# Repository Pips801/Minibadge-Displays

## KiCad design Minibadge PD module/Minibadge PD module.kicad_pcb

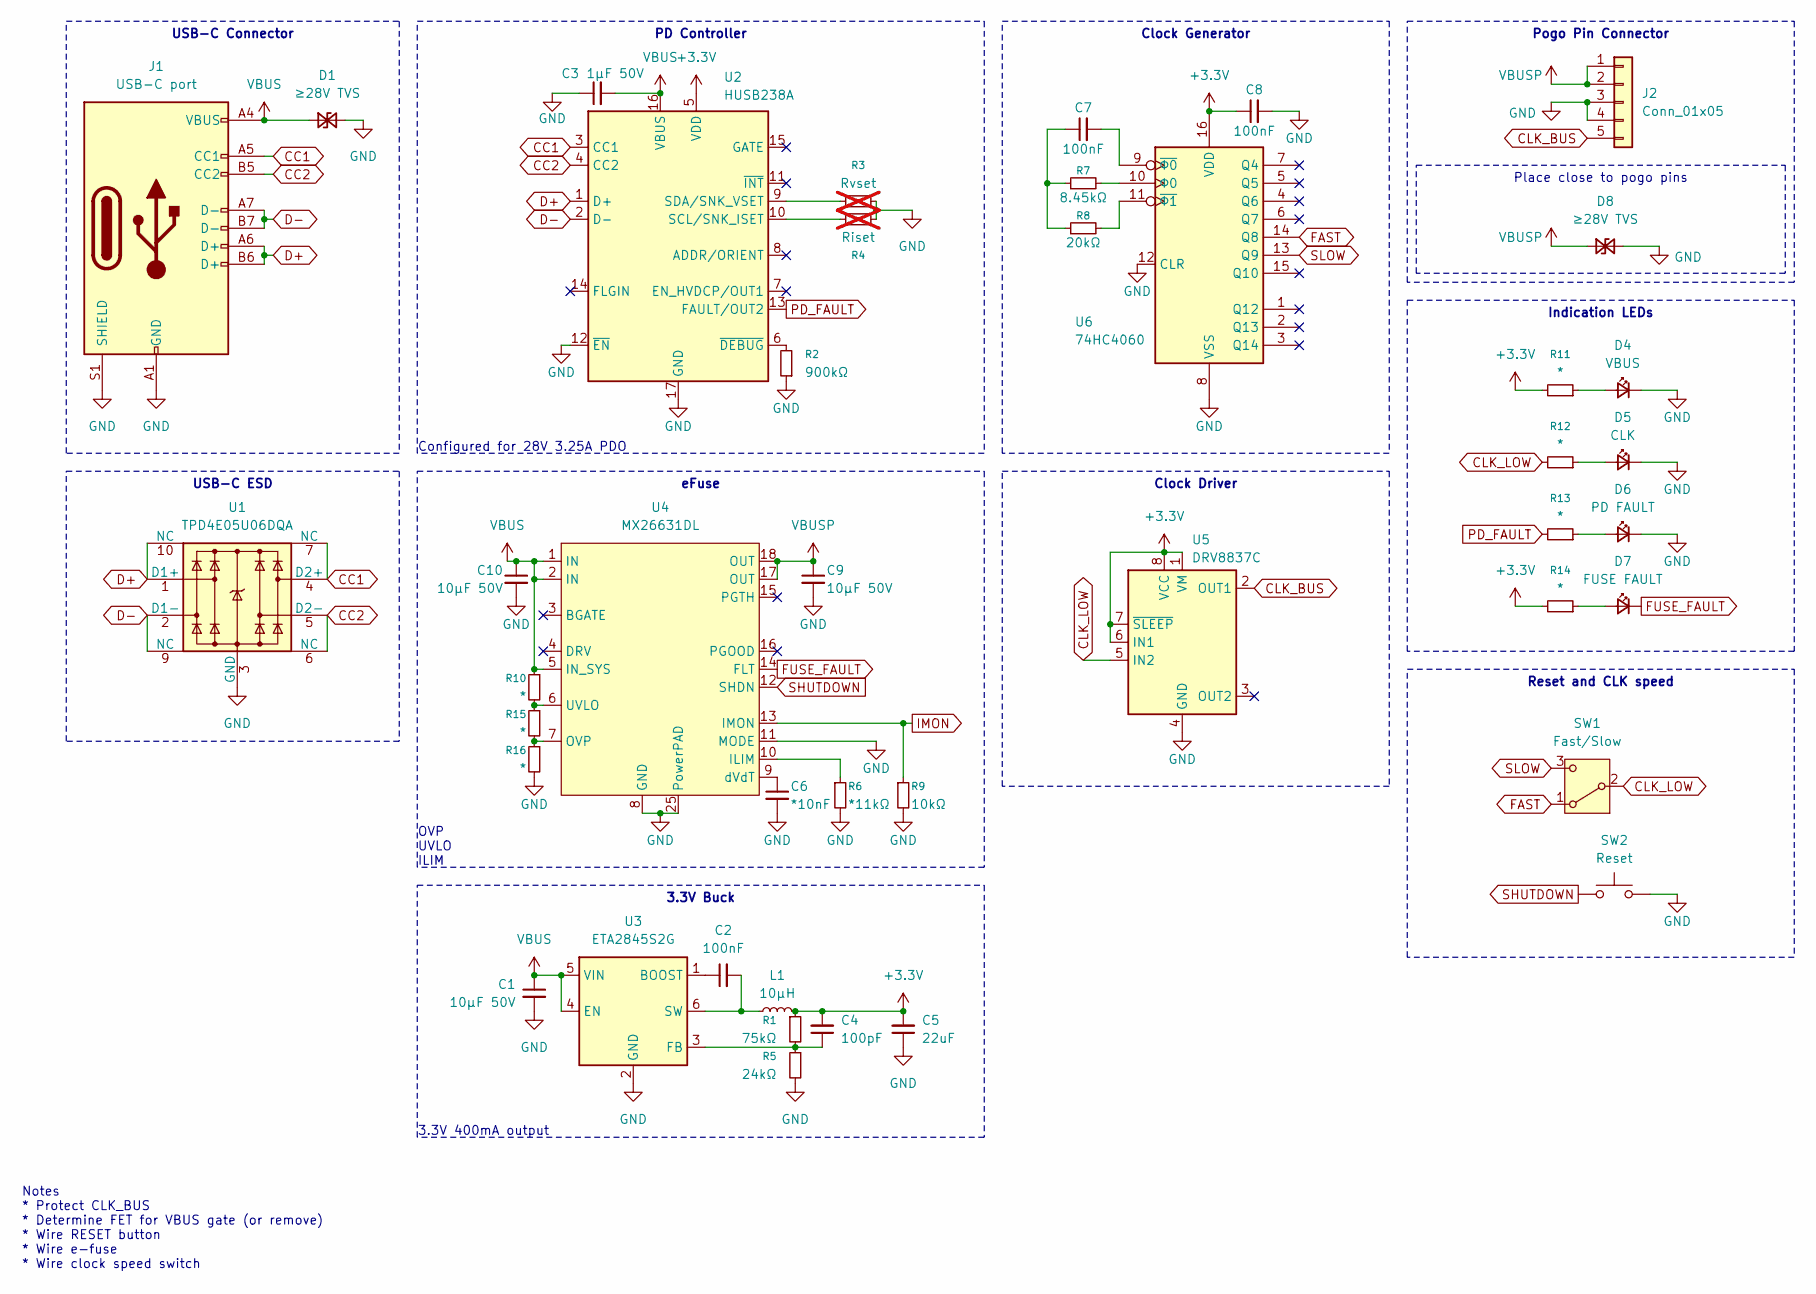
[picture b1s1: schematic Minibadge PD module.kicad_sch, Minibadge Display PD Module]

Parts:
C1, C9, C10: 10μF 50V; C_1206_3216Metric
C2, C7, C8: 100nF; C_0603_1608Metric
C3: 1μF 50V; C_0603_1608Metric
C4: 100pF; C_0603_1608Metric
C5: 22uF; C_1206_3216Metric
C6: *10nF; C_0603_1608Metric
D1, D8: ≥28V TVS; D_SMA
D4: VBUS; LED_0603_1608Metric
D5: CLK; LED_0603_1608Metric
D6: PD FAULT; LED_0603_1608Metric
D7: FUSE FAULT; LED_0603_1608Metric
J1: USB-C port; USB_C_Receptacle_HRO_TYPE-C-31-M-12
J2: Conn_01x05; PinHeader_1x05_P2.54mm_Horizontal
L1: 10μH; L_Taiyo-Yuden_MD-3030; LCSC Part # C668449
R1: 75kΩ; R_0603_1608Metric
R2: 900kΩ; R_0603_1608Metric
R3: Rvset; R_0603_1608Metric; not fitted
R4: Riset; R_0603_1608Metric; not fitted
R5: 24kΩ; R_0603_1608Metric
R6: *11kΩ; R_0603_1608Metric
R7: 8.45kΩ; R_0603_1608Metric
R8: 20kΩ; R_0603_1608Metric
R9: 10kΩ; R_0603_1608Metric
R10, R11, R12, R13, R14, R15, R16: *; R_0603_1608Metric
SW1: Fast/Slow
SW2: Reset
U1: TPD4E05U06DQA; USON-10_2.5x1.0mm_P0.5mm
U2: HUSB238A; WQFN-16-1EP_3x3mm_P0.5mm_EP1.75x1.75mm
U3: ETA2845S2G; TSOT-23-6; LCSC Part # C22362741
U4: MX26631DL; QFN-24-1EP_4x4mm_P0.5mm_EP2.6x2.6mm_ThermalVias
U5: DRV8837C; WSON-8-1EP_2x2mm_P0.5mm_EP0.9x1.6mm
U6: 74HC4060; TSSOP-16_4.4x5mm_P0.65mm

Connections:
+3.3V: C4.2, C5.2, C8.1, L1.2, R1.1, R11.2, R14.2, U2.5 (VDD), U5.1 (VM), U5.6 (IN1), U5.7 (~SLEEP), U5.8 (VCC), U6.16 (VDD)
CC1: J1.A5 (CC1), U1.4 (D2+), U1.7 (NC), U2.3 (CC1)
CC2: J1.B5 (CC2), U1.5 (D2-), U1.6 (NC), U2.4 (CC2)
CLK_BUS: J2.5, U5.2 (OUT1)
CLK_LOW: R12.2, SW1.2 (B), U5.5 (IN2)
D+: J1.A6 (D+), J1.B6 (D+), U1.1 (D1+), U1.10 (NC), U2.1 (D+)
D-: J1.A7 (D-), J1.B7 (D-), U1.2 (D1-), U1.9 (NC), U2.2 (D-)
FAST: SW1.1 (A), U6.14 (Q8)
FUSE_FAULT: D7.1 (K), U4.14 (FLT)
GND: C1.2, C3.1, C5.1, C6.2, C8.2, C9.2, C10.2, D1.2 (A2), D4.1 (K), D5.1 (K), D6.1 (K), D8.2 (A2), J1.A1 (GND), J1.A12 (GND), J1.B1 (GND), J1.B12 (GND), J1.S1 (SHIELD), J2.3, J2.4, R2.1, R3.2, R4.1, R5.2, R6.2, R9.2, R16.2, SW2.2, U1.3 (GND), U1.8 (GND), U2.12 (~EN), U2.17 (GND), U3.2 (GND), U4.8 (GND), U4.11 (MODE), U4.25 (PowerPAD), U5.4 (GND), U5.9 (GND), U6.8 (VSS), U6.12 (CLR)
IMON: R9.1, U4.13 (IMON)
unnamed: C7.1, R7.1, R8.1
unnamed: D4.2 (A), R11.1
unnamed: D5.2 (A), R12.1
unnamed: D6.2 (A), R13.1
unnamed: D7.2 (A), R14.1
unnamed: R4.2, U2.10 (SCL/SNK_ISET)
unnamed: R3.1, U2.9 (SDA/SNK_VSET)
unnamed: R2.2, U2.6 (~DEBUG)
unnamed: C2.1, U3.1 (BOOST)
unnamed: C4.1, R1.2, R5.1, U3.3 (FB)
unnamed: C2.2, L1.1, U3.6 (SW)
unnamed: R6.1, U4.10 (ILIM)
unnamed: R15.2, R16.1, U4.7 (OVP)
unnamed: R10.2, R15.1, U4.6 (UVLO)
unnamed: C6.1, U4.9 (dVdT)
unnamed: C7.2, U6.9 (~Φ0)
unnamed: R8.2, U6.11 (~Φ1)
unnamed: R7.2, U6.10 (Φ0)
PD_FAULT: R13.2, U2.13 (FAULT/OUT2)
SHUTDOWN: SW2.1, U4.12 (SHDN)
SLOW: SW1.3 (C), U6.13 (Q9)
VBUS: C1.1, C3.2, C10.1, D1.1 (A1), J1.A4 (VBUS), J1.A9 (VBUS), J1.B4 (VBUS), J1.B9 (VBUS), R10.1, U2.16 (VBUS), U3.4 (EN), U3.5 (VIN), U4.1 (IN), U4.2 (IN), U4.5 (IN_SYS)
VBUSP: C9.1, D8.1 (A1), J2.1, J2.2, U4.17 (OUT), U4.18 (OUT)

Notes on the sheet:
OVP UVLO ILIM
3.3V 400mA output
Notes * Protect CLK_BUS * Determine FET for VBUS gate (or remove) * Wire RESET button * Wire e-fuse * Wire clock speed switch
Configured for 28V 3.25A PDO
Reset and CLK speed
3.3V Buck
USB-C Connector
USB-C ESD
Clock Generator
Clock Driver
eFuse
Pogo Pin Connector
Indication LEDs
PD Controller
Place close to pogo pins

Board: 2 copper layers, 41 parts (0 on the bottom side), 31 nets, no tracks yet.

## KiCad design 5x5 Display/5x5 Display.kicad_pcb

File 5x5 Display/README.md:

# 5x5 Tileable Minibadge Display

## Details

A magnetically tileable 5x5 Minibadge display designed around USB-C PD input. This board accepts 5V - 28V and carries that voltage as the backplane for connected boards. Power input is regulated to 5V and 3.3V per board. It features a wide range of protections for shorts, over/under voltage, hotplugging, and ESD. 

### Features
* Wide voltage range input for various PD VBUS voltages (5V - 28V)
* Modular tileability using magnetic pogo pins
* Backplane scaleable to many hundreds of minibadges across many pannels

### Specifications
**Parameter**|**Value**
:-----:|:-----:
Input voltage|5V – 28V (USB-C PD)
Max input current|3.2A (Fuse-limited)
Minibadge rails|3.3V, 5V, CLK
Max output current|3.3V@3A, 5V@3A
Typical load|~13 W per board (3.3V@150mA per badge) 
Sockets|25 minibadges (5×5)
Indication|5V, 3V, CLK
Protection methods|TVS on connectors, ESD for CLK, Reverse polarity, Short protection

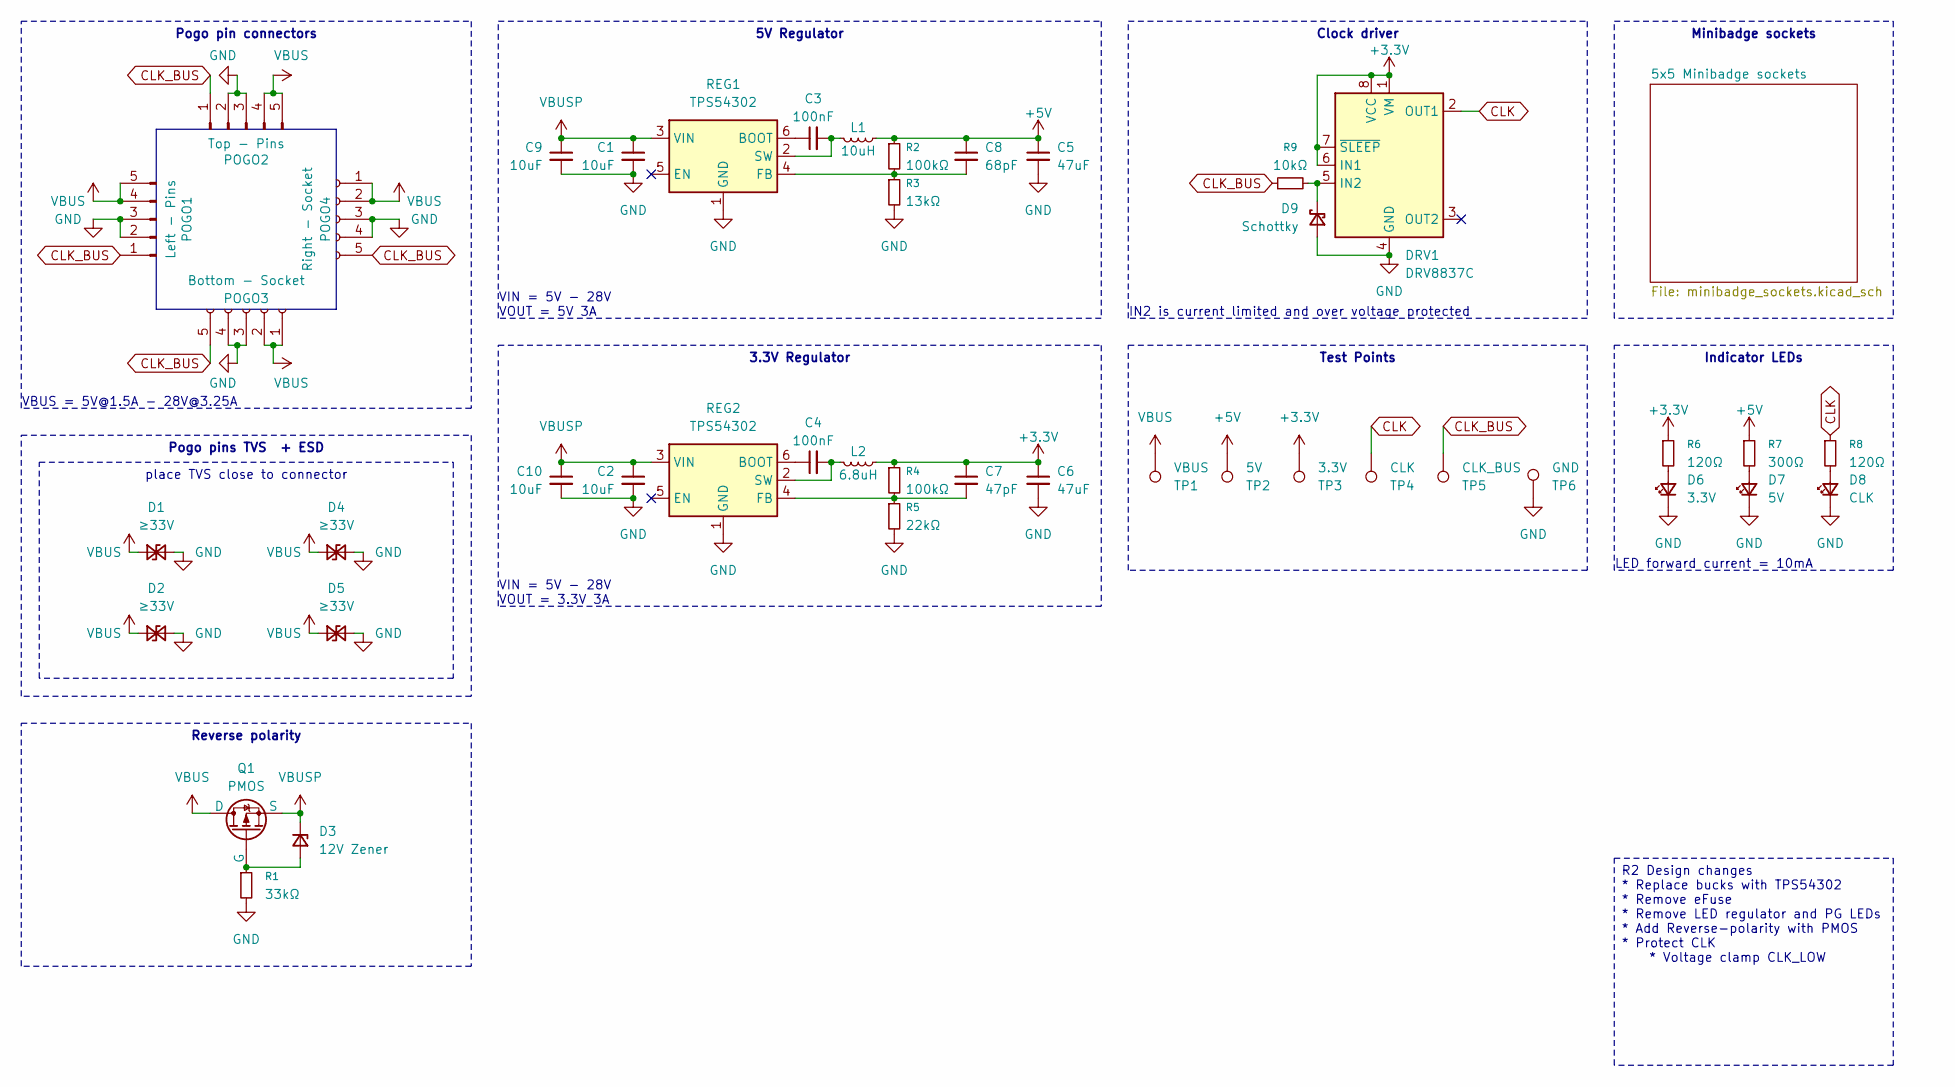
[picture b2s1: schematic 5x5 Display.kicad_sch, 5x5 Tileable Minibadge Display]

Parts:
C1, C2, C9, C10: 10uF; C_1206_3216Metric; LCSC Part # C13585
C3, C4: 100nF; C_0805_2012Metric; LCSC Part # C28233
C5, C6: 47uF; C_1206_3216Metric; LCSC Part # C96123
C7: 47pF; C_0603_1608Metric; LCSC Part # C1671
C8: 68pF; C_0603_1608Metric; LCSC Part # C28262
D1, D2, D4, D5: ≥33V; D_SMA; LCSC Part # C134981
D3: 12V Zener; D_SOD-123; LCSC Part # C22435092
D6: 3.3V; LED_0805_2012Metric; LCSC Part # C84256
D7: 5V; LED_0805_2012Metric; LCSC Part # C84256
D8: CLK; LED_0805_2012Metric; LCSC Part # C84256
D9: Schottky; D_SOD-123; LCSC Part # C7420325
DRV1: DRV8837C; WSON-8-1EP_2x2mm_P0.5mm_EP0.9x1.6mm; LCSC Part # C191000
L1: 10uH; L_TechFuse_SL0630; LCSC Part # C5189958
L2: 6.8uH; L_TechFuse_SL0630; LCSC Part # C5189749
POGO1: Left - Pins; PinSocket_1x05_P2.54mm_Horizontal
POGO2: Top - Pins; PinSocket_1x05_P2.54mm_Horizontal
POGO3: Bottom - Socket; PinSocket_1x05_P2.54mm_Horizontal
POGO4: Right - Socket; PinSocket_1x05_P2.54mm_Horizontal
Q1: PMOS; PQFN-8-EP_6x5mm_P1.27mm_Generic; LCSC Part # C51625746
R1: 33kΩ; R_0805_2012Metric
R2, R4: 100kΩ; R_0805_2012Metric; LCSC Part # C149504
R3: 13kΩ; R_0805_2012Metric; LCSC Part # C17455
R5: 22kΩ; R_0805_2012Metric; LCSC Part # C17560
R6, R8: 120Ω; R_0805_2012Metric; LCSC Part # C17437
R7: 300Ω; R_0805_2012Metric; LCSC Part # C17617
R9: 10kΩ; R_0805_2012Metric; LCSC Part # C17414
REG1, REG2: TPS54302; SOT-23-6; LCSC Part # C311983
TP1: VBUS; TestPoint_Pad_D1.5mm
TP2: 5V; TestPoint_Pad_D1.5mm
TP3: 3.3V; TestPoint_Pad_D1.5mm
TP4: CLK; TestPoint_Pad_D1.5mm
TP5: CLK_BUS; TestPoint_Pad_D1.5mm
TP6: GND; TestPoint_Pad_D1.5mm

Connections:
+3.3V: C6.1, C7.1, DRV1.1 (VM), DRV1.6 (IN1), DRV1.7 (~SLEEP), DRV1.8 (VCC), L2.2, R4.1, R6.1, TP3.1; also elsewhere on the board
+5V: C5.1, C8.1, L1.2, R2.1, R7.1, TP2.1; also elsewhere on the board
CLK: DRV1.2 (OUT1), R8.1, TP4.1; also elsewhere on the board
CLK_BUS: POGO1.1, POGO2.1, POGO3.5, POGO4.5, R9.1, TP5.1
GND: C1.2, C2.2, C5.2, C6.2, C9.2, C10.2, D1.2 (A2), D2.2 (A2), D4.2 (A2), D5.2 (A2), D6.1 (K), D7.1 (K), D8.1 (K), D9.2 (A), DRV1.4 (GND), DRV1.9 (GND), POGO1.2, POGO1.3, POGO2.2, POGO2.3, POGO3.3, POGO3.4, POGO4.3, POGO4.4, R1.2, R3.2, R5.2, REG1.1 (GND), REG2.1 (GND), TP6.1; also elsewhere on the board
unnamed: D3.2 (A), Q1.4 (G), R1.1
unnamed: D6.2 (A), R6.2
unnamed: D7.2 (A), R7.2
unnamed: D8.2 (A), R8.2
unnamed: D9.1 (K), DRV1.5 (IN2), R9.2
unnamed: C3.1, REG1.6 (BOOT)
unnamed: C8.2, R2.2, R3.1, REG1.4 (FB)
unnamed: C3.2, L1.1, REG1.2 (SW)
unnamed: C4.1, REG2.6 (BOOT)
unnamed: C7.2, R4.2, R5.1, REG2.4 (FB)
unnamed: C4.2, L2.1, REG2.2 (SW)
VBUS: D1.1 (A1), D2.1 (A1), D4.1 (A1), D5.1 (A1), POGO1.4, POGO1.5, POGO2.4, POGO2.5, POGO3.1, POGO3.2, POGO4.1, POGO4.2, Q1.5 (D), Q1.6 (D), Q1.7 (D), Q1.8 (D), Q1.9 (D), TP1.1
VBUSP: C1.1, C2.1, C9.1, C10.1, D3.1 (K), Q1.1 (S), Q1.2 (S), Q1.3 (S), REG1.3 (VIN), REG2.3 (VIN)

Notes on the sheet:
LED forward current = 10mA
VBUS = 5V@1.5A - 28V@3.25A
VIN = 5V - 28V VOUT = 5V 3A
IN2 is current limited and over voltage protected
VIN = 5V - 28V VOUT = 3.3V 3A
3.3V Regulator
Reverse polarity
Clock driver
place TVS close to connector
Test Points
Indicator LEDs
Pogo pins TVS + ESD
Pogo pin connectors
Minibadge sockets
R2 Design changes * Replace bucks with TPS54302 * Remove eFuse * Remove LED regulator and PG LEDs * Add Reverse-polarity with PMOS * Protect CLK * Voltage clamp CLK_LOW
5V Regulator

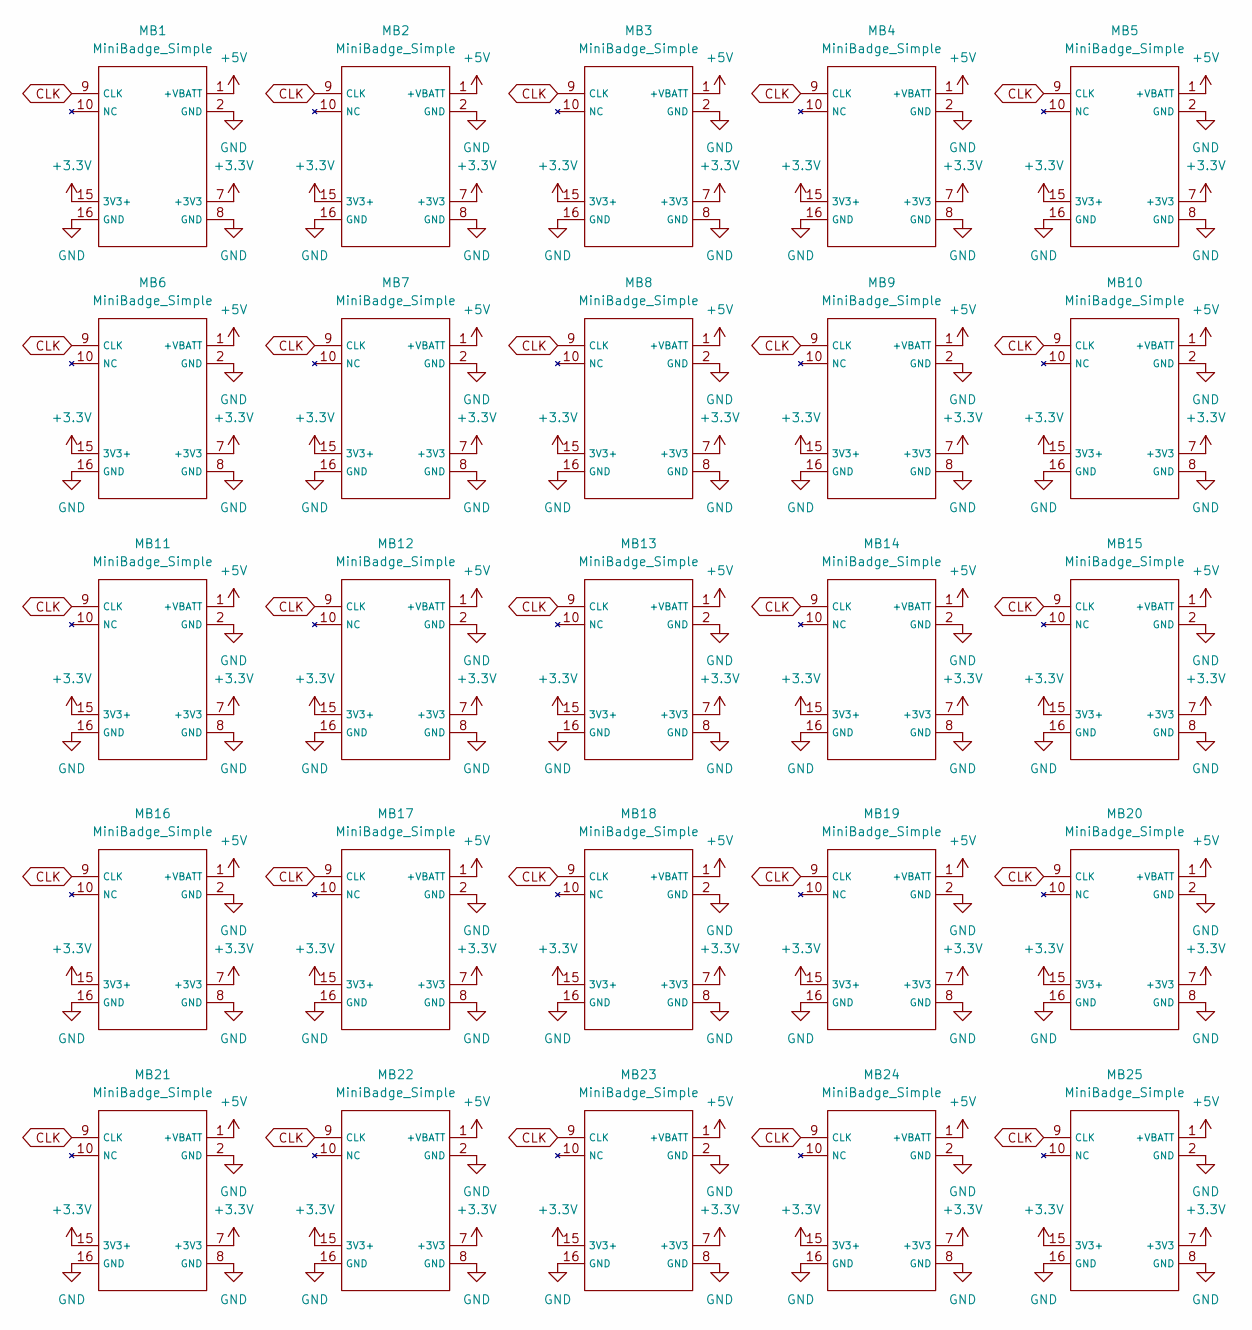
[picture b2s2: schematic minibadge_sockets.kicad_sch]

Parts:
MB1, MB2, MB3, MB4, MB5, MB6, MB7, MB8, MB9, MB10, MB11, MB12, MB13, MB14, MB15, MB16, MB17, MB18, MB19, MB20, MB21, MB22, MB23, MB24, MB25: MiniBadge_Simple; MiniBadge_Slot_Reflective

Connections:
+3.3V: MB1.7 (+3V3), MB1.15 (3V3+), MB2.7 (+3V3), MB2.15 (3V3+), MB3.7 (+3V3), MB3.15 (3V3+), MB4.7 (+3V3), MB4.15 (3V3+), MB5.7 (+3V3), MB5.15 (3V3+), MB6.7 (+3V3), MB6.15 (3V3+), MB7.7 (+3V3), MB7.15 (3V3+), MB8.7 (+3V3), MB8.15 (3V3+), MB9.7 (+3V3), MB9.15 (3V3+), MB10.7 (+3V3), MB10.15 (3V3+), MB11.7 (+3V3), MB11.15 (3V3+), MB12.7 (+3V3), MB12.15 (3V3+), MB13.7 (+3V3), MB13.15 (3V3+), MB14.7 (+3V3), MB14.15 (3V3+), MB15.7 (+3V3), MB15.15 (3V3+), MB16.7 (+3V3), MB16.15 (3V3+), MB17.7 (+3V3), MB17.15 (3V3+), MB18.7 (+3V3), MB18.15 (3V3+), MB19.7 (+3V3), MB19.15 (3V3+), MB20.7 (+3V3), MB20.15 (3V3+), MB21.7 (+3V3), MB21.15 (3V3+), MB22.7 (+3V3), MB22.15 (3V3+), MB23.7 (+3V3), MB23.15 (3V3+), MB24.7 (+3V3), MB24.15 (3V3+), MB25.7 (+3V3), MB25.15 (3V3+); also elsewhere on the board
+5V: MB1.1 (+VBATT), MB2.1 (+VBATT), MB3.1 (+VBATT), MB4.1 (+VBATT), MB5.1 (+VBATT), MB6.1 (+VBATT), MB7.1 (+VBATT), MB8.1 (+VBATT), MB9.1 (+VBATT), MB10.1 (+VBATT), MB11.1 (+VBATT), MB12.1 (+VBATT), MB13.1 (+VBATT), MB14.1 (+VBATT), MB15.1 (+VBATT), MB16.1 (+VBATT), MB17.1 (+VBATT), MB18.1 (+VBATT), MB19.1 (+VBATT), MB20.1 (+VBATT), MB21.1 (+VBATT), MB22.1 (+VBATT), MB23.1 (+VBATT), MB24.1 (+VBATT), MB25.1 (+VBATT); also elsewhere on the board
CLK: MB1.9 (CLK), MB2.9 (CLK), MB3.9 (CLK), MB4.9 (CLK), MB5.9 (CLK), MB6.9 (CLK), MB7.9 (CLK), MB8.9 (CLK), MB9.9 (CLK), MB10.9 (CLK), MB11.9 (CLK), MB12.9 (CLK), MB13.9 (CLK), MB14.9 (CLK), MB15.9 (CLK), MB16.9 (CLK), MB17.9 (CLK), MB18.9 (CLK), MB19.9 (CLK), MB20.9 (CLK), MB21.9 (CLK), MB22.9 (CLK), MB23.9 (CLK), MB24.9 (CLK), MB25.9 (CLK); also elsewhere on the board
GND: MB1.2 (GND), MB1.8 (GND), MB1.16 (GND), MB2.2 (GND), MB2.8 (GND), MB2.16 (GND), MB3.2 (GND), MB3.8 (GND), MB3.16 (GND), MB4.2 (GND), MB4.8 (GND), MB4.16 (GND), MB5.2 (GND), MB5.8 (GND), MB5.16 (GND), MB6.2 (GND), MB6.8 (GND), MB6.16 (GND), MB7.2 (GND), MB7.8 (GND), MB7.16 (GND), MB8.2 (GND), MB8.8 (GND), MB8.16 (GND), MB9.2 (GND), MB9.8 (GND), MB9.16 (GND), MB10.2 (GND), MB10.8 (GND), MB10.16 (GND), MB11.2 (GND), MB11.8 (GND), MB11.16 (GND), MB12.2 (GND), MB12.8 (GND), MB12.16 (GND), MB13.2 (GND), MB13.8 (GND), MB13.16 (GND), MB14.2 (GND), MB14.8 (GND), MB14.16 (GND), MB15.2 (GND), MB15.8 (GND), MB15.16 (GND), MB16.2 (GND), MB16.8 (GND), MB16.16 (GND), MB17.2 (GND), MB17.8 (GND), MB17.16 (GND), MB18.2 (GND), MB18.8 (GND), MB18.16 (GND), MB19.2 (GND), MB19.8 (GND), MB19.16 (GND), MB20.2 (GND), MB20.8 (GND), MB20.16 (GND), MB21.2 (GND), MB21.8 (GND), MB21.16 (GND), MB22.2 (GND), MB22.8 (GND), MB22.16 (GND), MB23.2 (GND), MB23.8 (GND), MB23.16 (GND), MB24.2 (GND), MB24.8 (GND), MB24.16 (GND), MB25.2 (GND), MB25.8 (GND), MB25.16 (GND); also elsewhere on the board

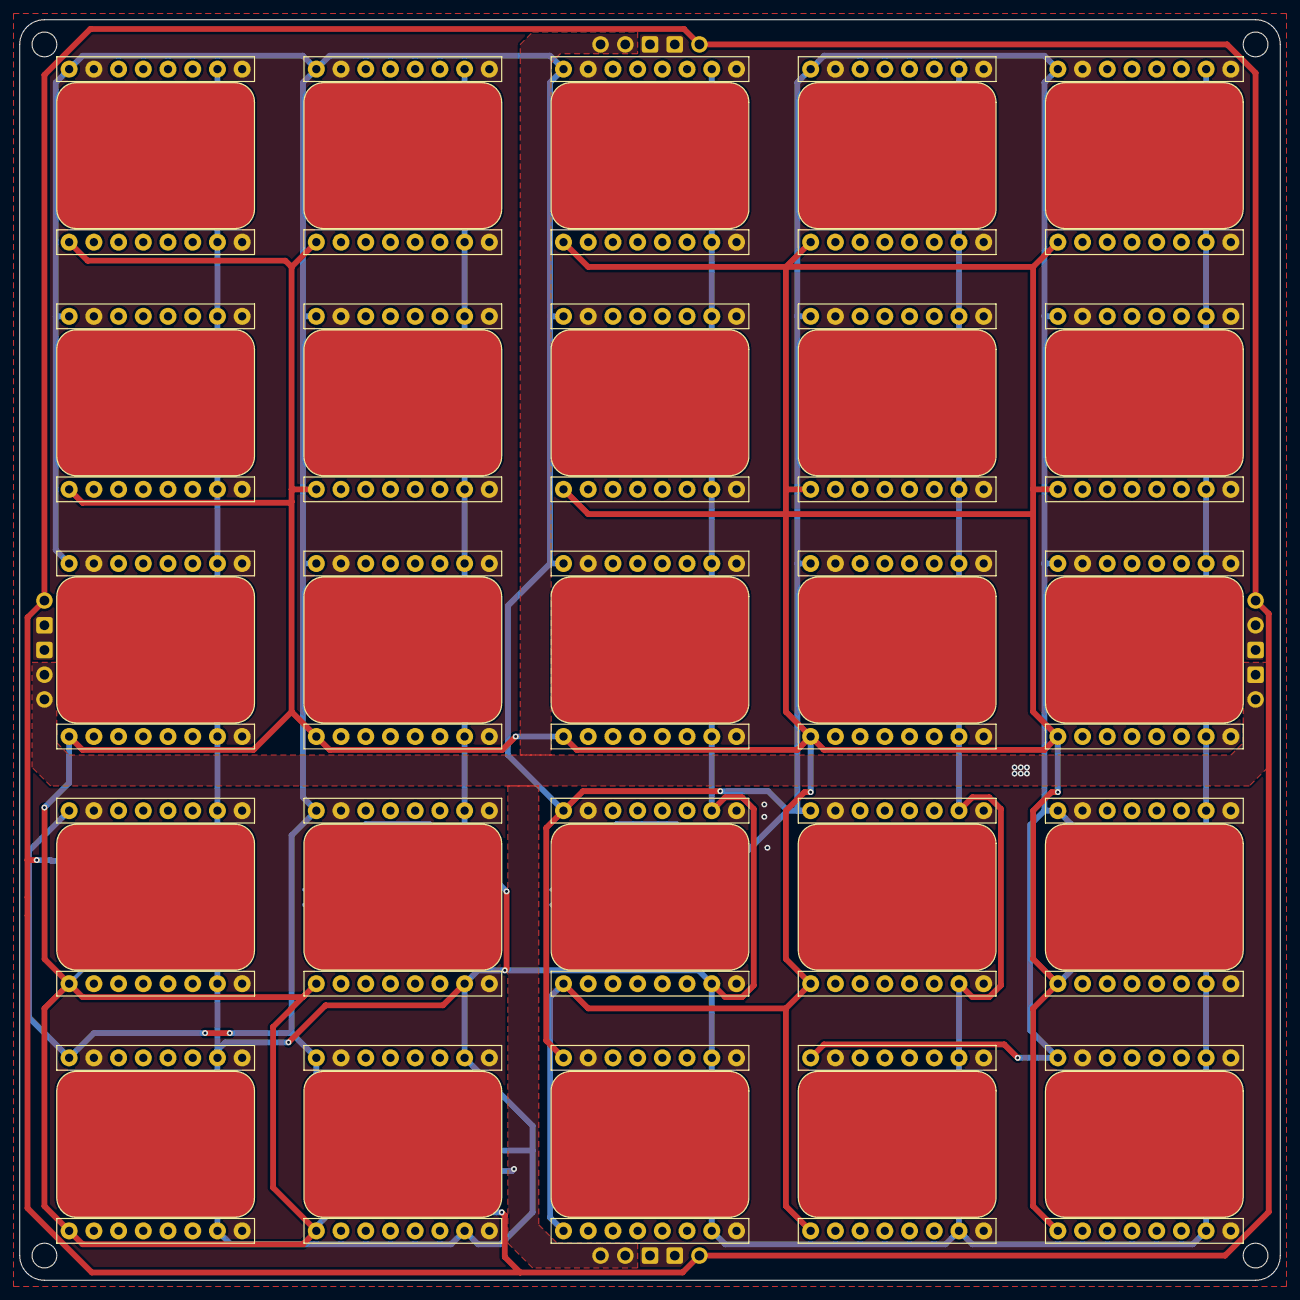
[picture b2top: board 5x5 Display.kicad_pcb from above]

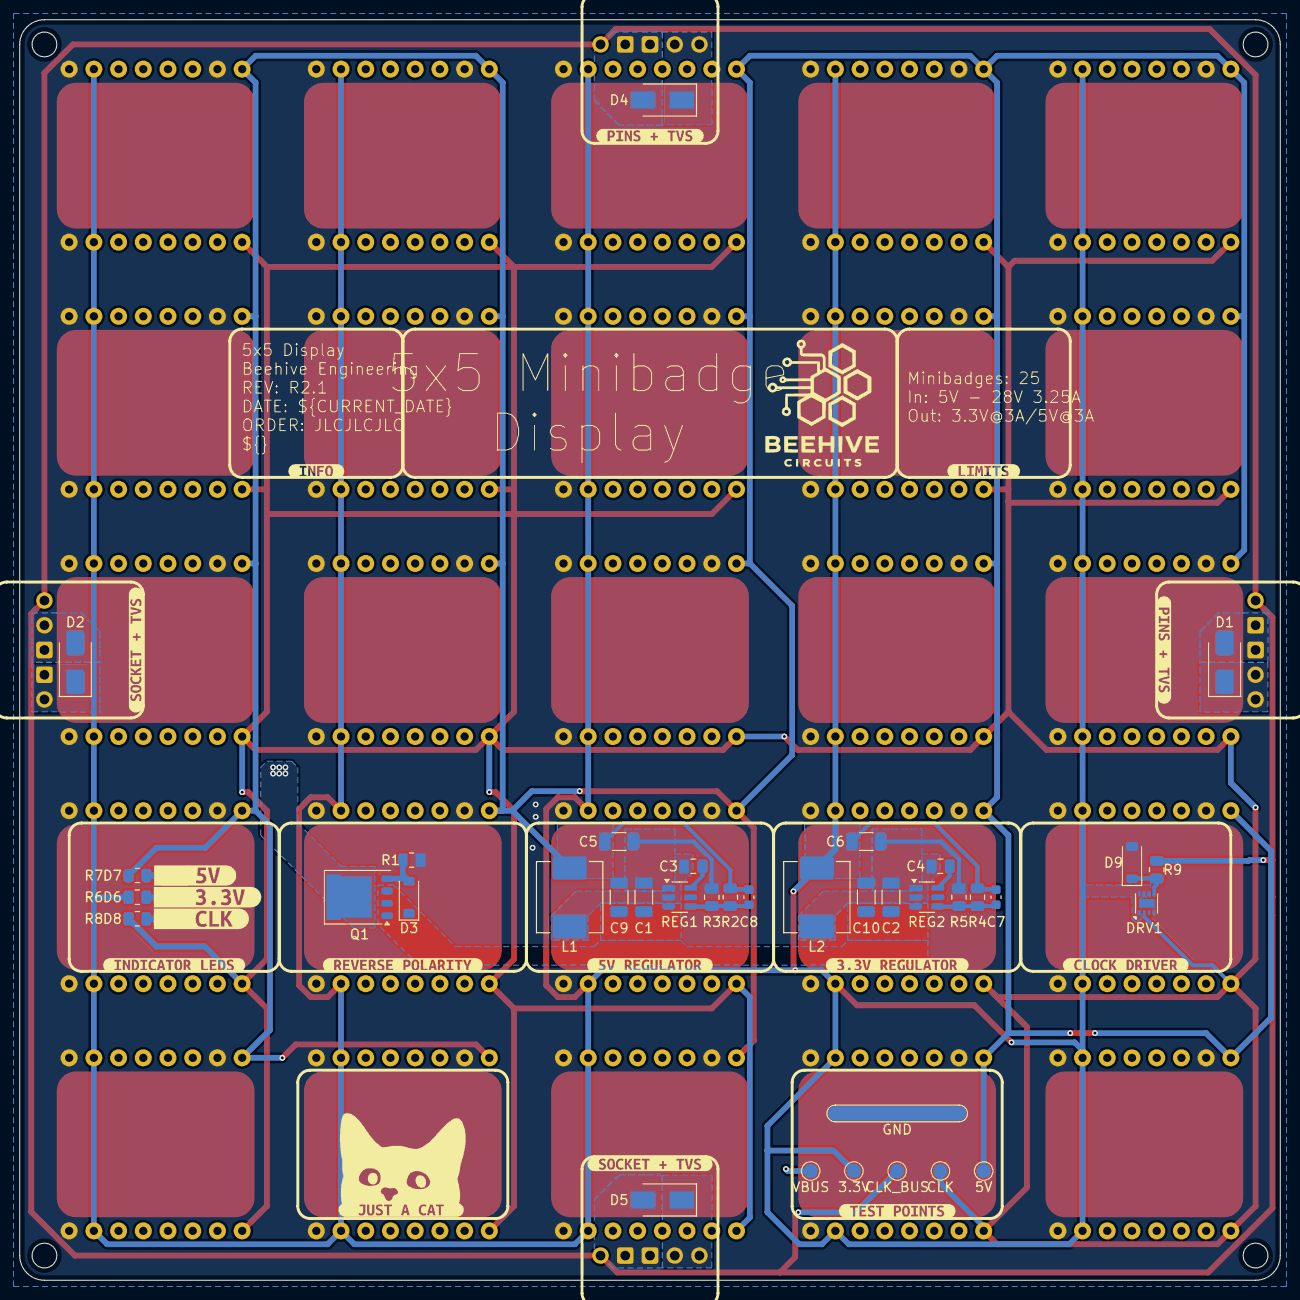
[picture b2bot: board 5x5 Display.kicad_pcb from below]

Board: 2 copper layers, 129.5 x 129.5 mm, 86 parts (57 on the bottom side), 18 nets.

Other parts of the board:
kibuzzard-696F0B33: G***; kibuzzard-696F0B33
kibuzzard-696F07FC: G***; kibuzzard-696F07FC
kibuzzard-696F09B6: G***; kibuzzard-696F09B6
kibuzzard-696F080D: G***; kibuzzard-696F080D
kibuzzard-696F081C: G***; kibuzzard-696F081C
kibuzzard-696F082C: G***; kibuzzard-696F082C
kibuzzard-696F097A: G***; kibuzzard-696F097A
kibuzzard-696F0995: G***; kibuzzard-696F0995
kibuzzard-696F1606: G***; kibuzzard-696F1606
kibuzzard-69658F74: G***; kibuzzard-69658F74
kibuzzard-69658FBF: G***; kibuzzard-69658FBF
kibuzzard-69658FCE: G***; kibuzzard-69658FCE
kibuzzard-69658FDE: G***; kibuzzard-69658FDE
kibuzzard-6965973E: G***; kibuzzard-6965973E
kibuzzard-69659724: G***; kibuzzard-69659724
kibuzzard-69659941: G***; kibuzzard-69659941
logo1: Beehive Logo; LOGO

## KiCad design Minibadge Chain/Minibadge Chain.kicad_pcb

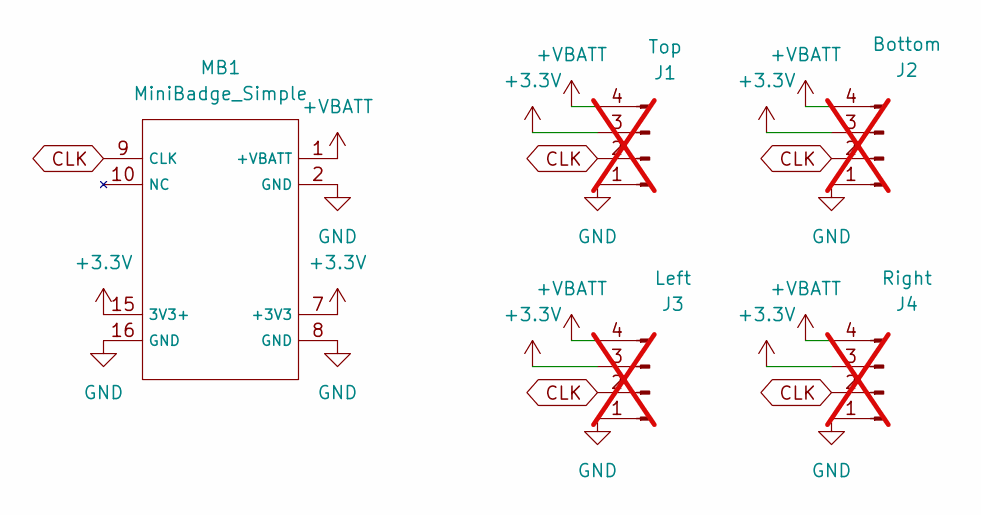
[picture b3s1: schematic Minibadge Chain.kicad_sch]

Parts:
J1: Top; PinSocket_1x04_P2.54mm_Vertical; not fitted
J2: Bottom; PinSocket_1x04_P2.54mm_Vertical; not fitted
J3: Left; PinSocket_1x04_P2.54mm_Vertical; not fitted
J4: Right; PinSocket_1x04_P2.54mm_Vertical; not fitted
MB1: MiniBadge_Simple; MiniBadge_Slot_Reflective

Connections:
+3.3V: J1.3, J2.3, J3.3, J4.3, MB1.7 (+3V3), MB1.15 (3V3+)
+VBATT: J1.4, J2.4, J3.4, J4.4, MB1.1 (+VBATT)
CLK: J1.2, J2.2, J3.2, J4.2, MB1.9 (CLK)
GND: J1.1, J2.1, J3.1, J4.1, MB1.2 (GND), MB1.8 (GND), MB1.16 (GND)

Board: 4 copper layers, 5 parts (4 on the bottom side), 4 nets, no tracks yet.

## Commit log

2025-11-21 Minibadge Chain
2026-01-10 5x5 grid initial commit
2026-01-10 Update schematic wiring and component positions
    Adjusted wire routing and junctions around the 58.42mm y-coordinate, updated positions of R2 and R3, and changed some property values for clarity. These changes improve schematic readability and corr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
2026-01-10 Add README for 5x5 Tileable Minibadge Display
    This README provides an overview of the 5x5 Tileable Minibadge Display, detailing its design goals, specifications, and protection features.
2026-01-10 Change 'Design Goals' to 'Features' in README
    Updated section title from 'Design Goals' to 'Features' in README.
2026-01-10 Add TPS56637 VQFN-HR (10) footprint and 3D model
    Added the KiCad footprint and STEP 3D model for the TPS56637 VQFN-HR (10) package. Updated the fp-lib-table to include the new footprint library.
2026-01-10 Footprint assignment finished
2026-01-10 Add test points to schematic
2026-01-10 Assign test point footprints in schematic
    Set the 'Footprint' property to 'TestPoint:TestPoint_Pad_D1.5mm' for multiple components in the 5x5 Display schematic. This change ensures correct footprint assignment for test points in PCB layout.
2026-01-11 buck layout
2026-01-11 Initial route complete
2026-01-11 Fix CLK_LOW routing
2026-01-12 Add silkscreen text, rectangle, and tented vias
    Added a large silkscreen label '5X5 DISPLAY PROTOTYPE' and a rectangle to the PCB. Adjusted the positions of several component references. Enabled tenting on multiple vias for nets 2, 4, and 9. Updat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
2026-01-13 Silkscreens and components
2026-01-14 Planning PD module
2026-01-15 R2 initial commit
    * remove eFuse
    * remove LED regulator
    * swap bucks for cheaper ones
    * add reverse polarity
2026-01-19 R2
    R2 changes
    - Reverse polarity protection
    - clamp voltage on CLK_BUS
    - cheaper regulators
    - removal of eFuse (will be upstream on PD module)
    - removal of Power Good architecture
2026-01-20 R2 updates
    * Component selection and footprint finished
    * Added feed-forward capacitor
    * Increased capacitance for Cin
2026-01-20 R2 board routed
2026-01-20 Add test points
2026-01-20 fix minibadge footprint
2026-01-20 remove pogo pin graphics
2026-01-20 update LCSC part number for bootstrap capacitors
2026-01-20 R2 Ordered
2026-01-20 R2.1
    Fix Cin pours for regulators
2026-01-20 Revise output current and protection methods in README
    Updated specifications and features for clarity and accuracy.
2026-01-21 PD module work
